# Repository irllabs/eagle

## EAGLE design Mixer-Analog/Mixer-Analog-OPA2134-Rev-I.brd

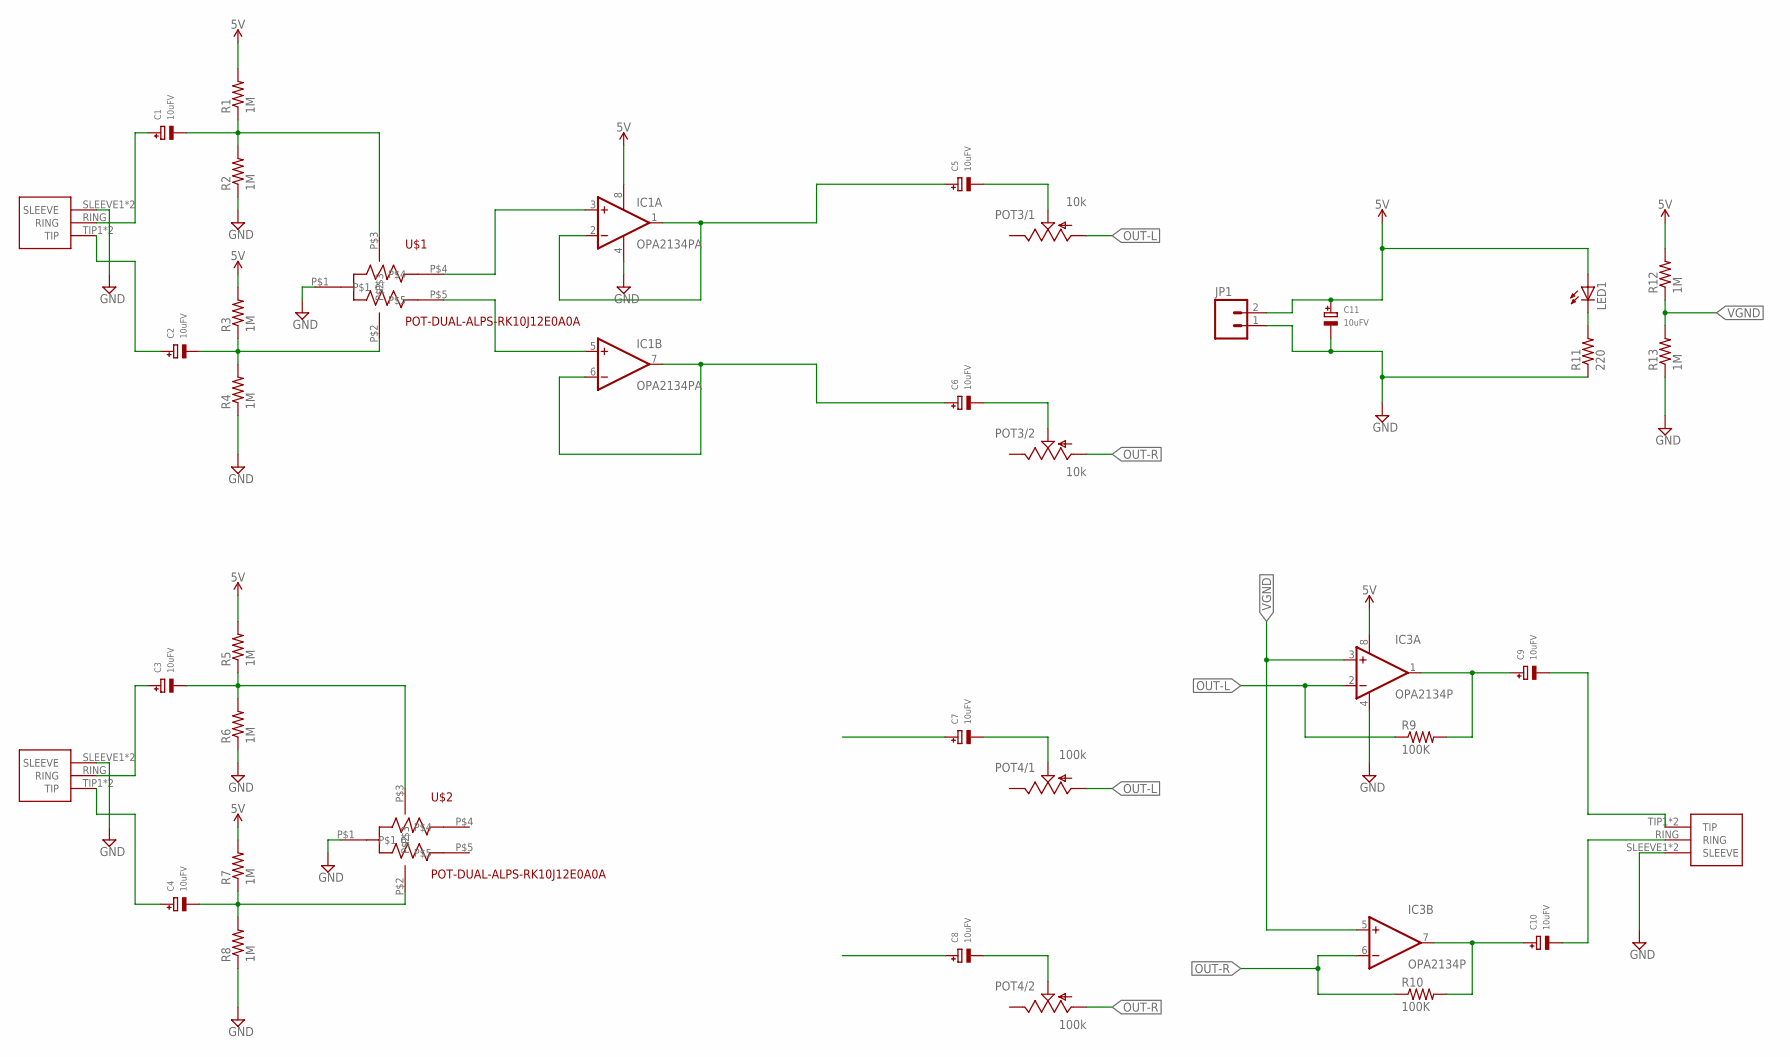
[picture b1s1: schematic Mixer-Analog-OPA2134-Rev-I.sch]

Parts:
C1, C2, C3, C4, C5, C6, C7, C8, C9, C10, C11: 10uFV; CELEC_3.5MM_8MM
IC1: OPA2134PA; DIL08
IC3: OPA2134P; DIL08
J1, J2, J3: 1/8"-F-STEREO-PCB
JP1: M02LOCK; 1X02_LOCK
LED1: LED3MM
POT3: 10k; PTV112
POT4: 100k; PTV112
R1, R3, R4, R5, R6, R7, R8, R12, R13: 1M; AXIAL-0.3EZ
R2: 1M; AXIAL-0.3
R9, R10: 100K; AXIAL-0.3EZ
R11: 220; AXIAL-0.3EZ
U$1, U$2: POT-DUAL-ALPS-RK10J12E0A0A

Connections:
5V: C11.+, IC1.8 (V+), IC3.8 (V+), JP1.2, LED1.A, R1.P$2 (2), R3.P$2 (2), R5.P$2 (2), R7.P$2 (2), R12.P$2 (2)
GND: C11.-, IC1.4 (V-), IC3.4 (V-), J1.SLEEVE1 (SLEEVE), J1.SLEEVE2 (SLEEVE), J2.SLEEVE1 (SLEEVE), J2.SLEEVE2 (SLEEVE), J3.SLEEVE1 (SLEEVE), J3.SLEEVE2 (SLEEVE), JP1.1, R2.P$1 (1), R4.P$1 (1), R6.P$1 (1), R8.P$1 (1), R11.P$1 (1), R13.P$1 (1), U$1.P$1, U$2.P$1
unnamed: C5.-, POT3.1.2 (S)
unnamed: C2.-, R3.P$1 (1), R4.P$2 (2), U$1.P$2
unnamed: C1.+, J1.RING
unnamed: C6.-, POT3.2.2 (S)
unnamed: C9.+, IC3.1 (OUT), R9.P$2 (2)
unnamed: IC1.3 (+IN), U$1.P$4
unnamed: C2.+, J1.TIP1 (TIP), J1.TIP2 (TIP)
unnamed: C7.-, POT4.1.2 (S)
unnamed: C8.-, POT4.2.2 (S)
unnamed: C4.-, R7.P$1 (1), R8.P$2 (2), U$2.P$2
unnamed: C3.+, J2.RING
unnamed: C4.+, J2.TIP1 (TIP), J2.TIP2 (TIP)
unnamed: LED1.K (C), R11.P$2 (2)
unnamed: C10.+, IC3.7 (OUT), R10.P$2 (2)
unnamed: IC1.5 (+IN), U$1.P$5
unnamed: C6.+, IC1.6 (-IN), IC1.7 (OUT)
unnamed: C3.-, R5.P$1 (1), R6.P$2 (2), U$2.P$3
unnamed: C1.-, R1.P$1 (1), R2.P$2 (2), U$1.P$3
unnamed: C9.-, J3.TIP1 (TIP), J3.TIP2 (TIP)
unnamed: C10.-, J3.RING
OUT-L: IC3.2 (-IN), POT3.1.1 (A), POT4.1.1 (A), R9.P$1 (1)
OUT-R: IC3.6 (-IN), POT3.2.1 (A), POT4.2.1 (A), R10.P$1 (1)
POT1: C5.+, IC1.1 (OUT), IC1.2 (-IN)
VGND: IC3.3 (+IN), IC3.5 (+IN), R12.P$1 (1), R13.P$2 (2)

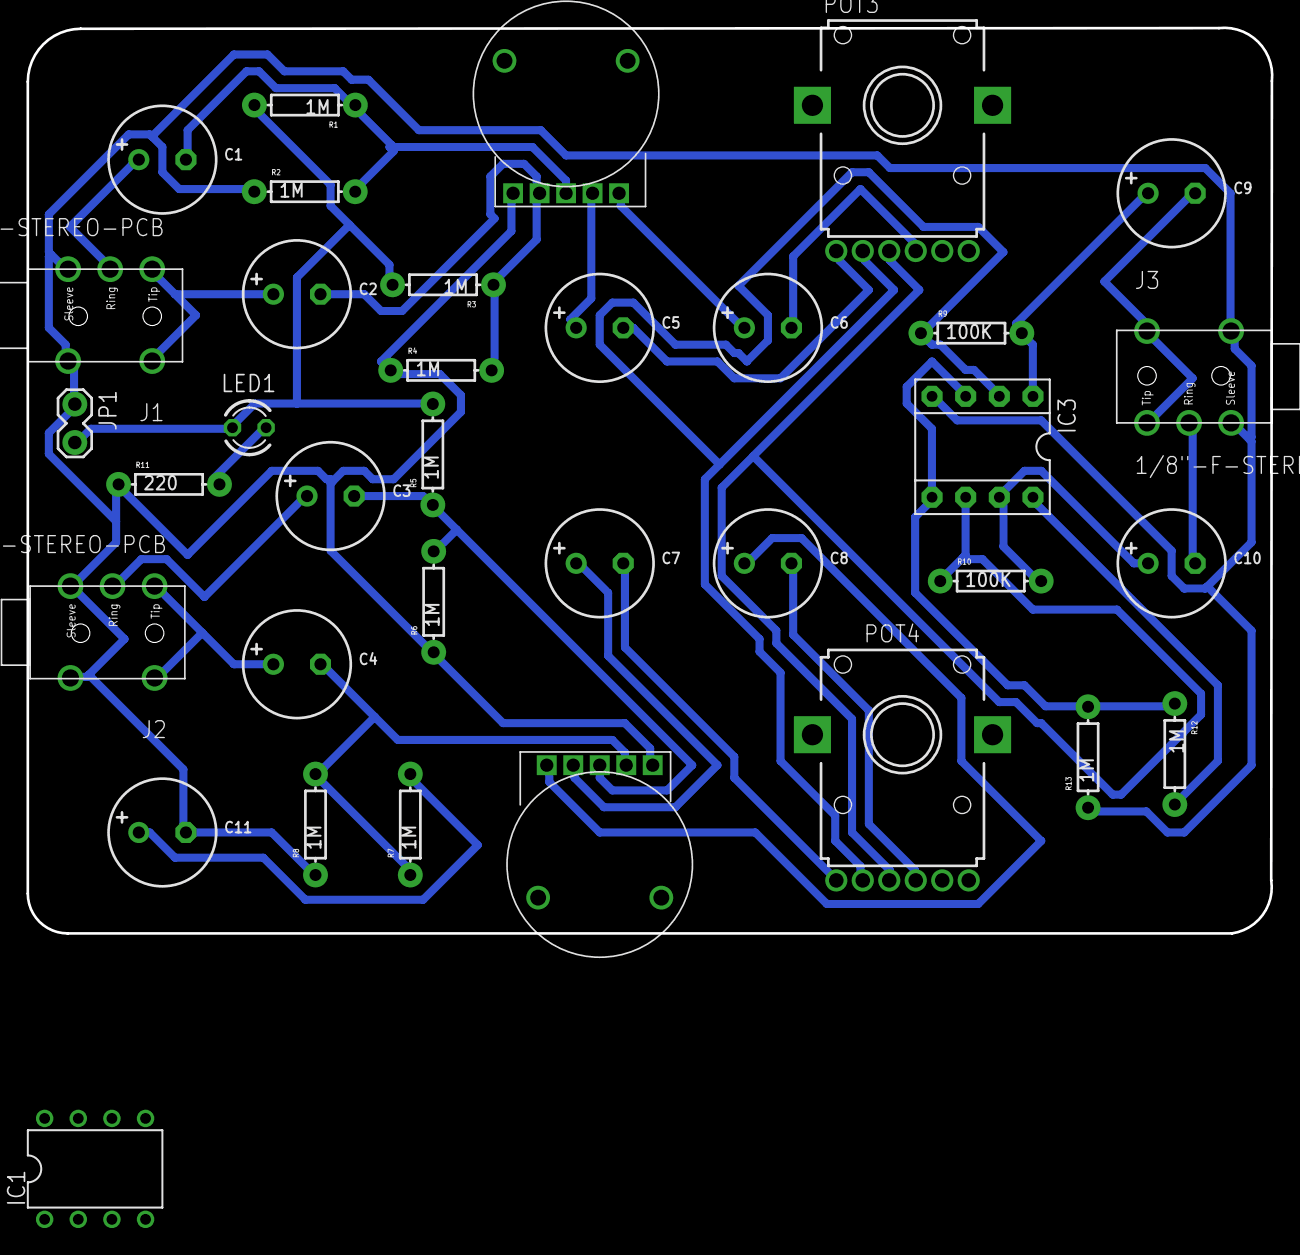
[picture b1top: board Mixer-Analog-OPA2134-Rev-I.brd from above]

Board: 2 copper layers, 94.0 x 68.4 mm, 35 parts (0 on the bottom side), 26 nets.

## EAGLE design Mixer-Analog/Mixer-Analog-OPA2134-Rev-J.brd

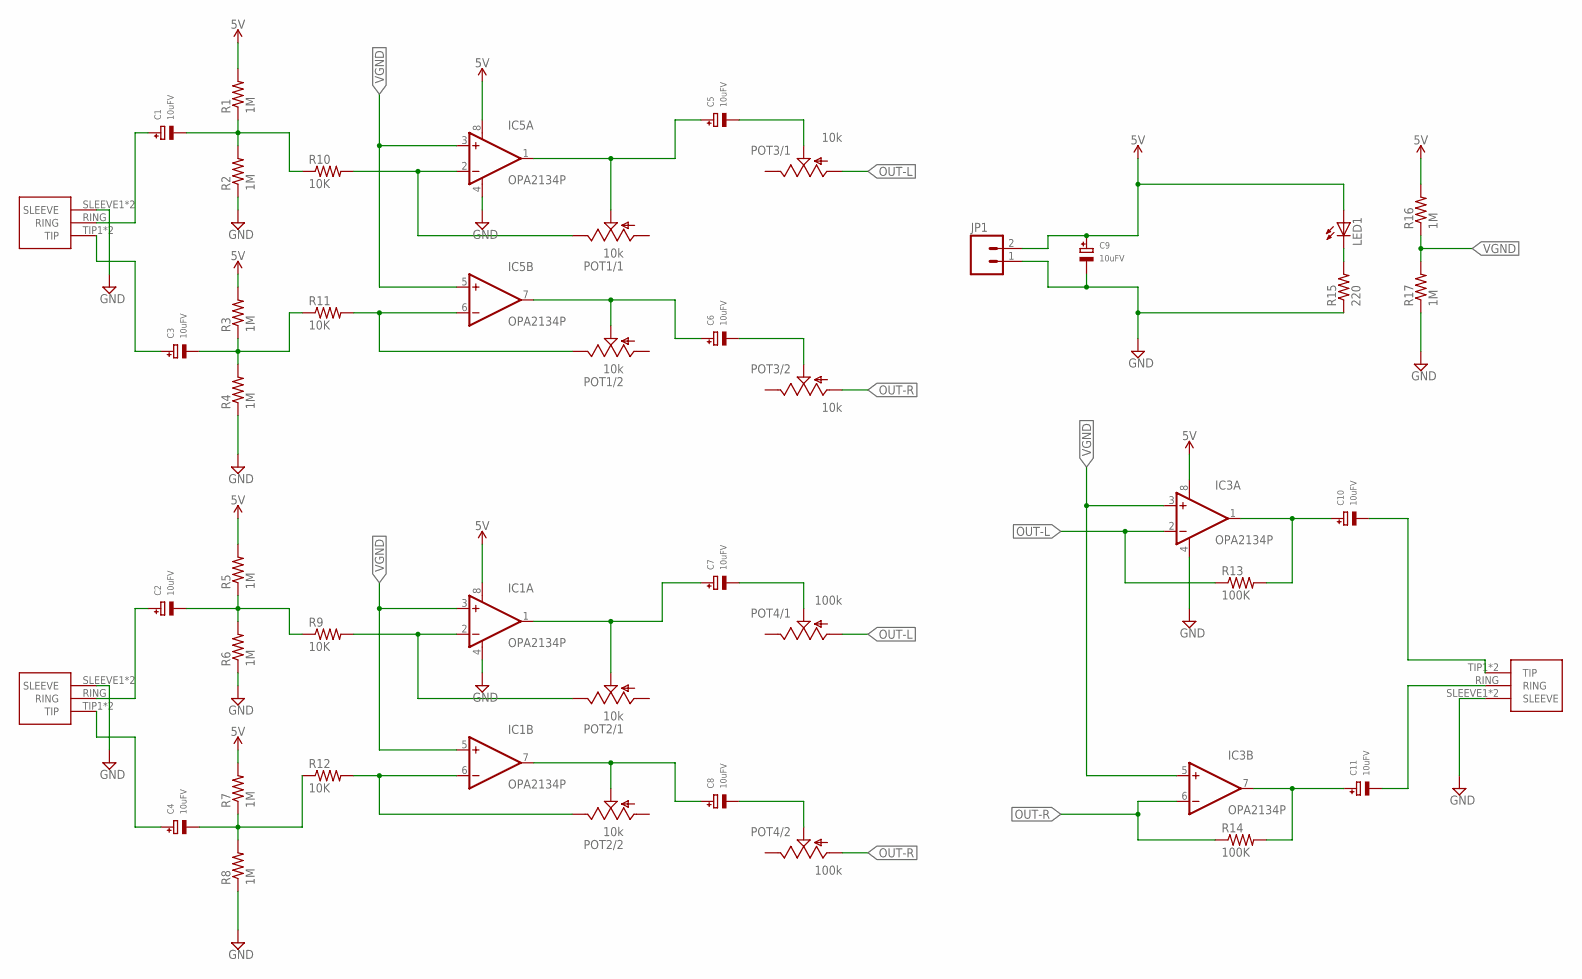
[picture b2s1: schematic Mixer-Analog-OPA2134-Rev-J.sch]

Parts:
C1, C2, C3, C4, C5, C6, C7, C8, C9, C10, C11: 10uFV; CELEC_3.5MM_8MM
IC1, IC3, IC5: OPA2134P; DIL08
J1, J2, J3: 1/8"-F-STEREO-PCB
JP1: M02LOCK; 1X02_LOCK
LED1: LED3MM
POT1, POT2, POT3: 10k; PTV112
POT4: 100k; PTV112
R1, R3, R4, R5, R6, R7, R8, R16, R17: 1M; AXIAL-0.3EZ
R2: 1M; AXIAL-0.3
R9, R10, R11, R12: 10K; AXIAL-0.3EZ
R13, R14: 100K; AXIAL-0.3EZ
R15: 220; AXIAL-0.3EZ

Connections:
5V: C9.+, IC1.8 (V+), IC3.8 (V+), IC5.8 (V+), JP1.2, LED1.A, R1.P$2 (2), R3.P$2 (2), R5.P$2 (2), R7.P$2 (2), R16.P$2 (2)
GND: C9.-, IC1.4 (V-), IC3.4 (V-), IC5.4 (V-), J1.SLEEVE1 (SLEEVE), J1.SLEEVE2 (SLEEVE), J2.SLEEVE1 (SLEEVE), J2.SLEEVE2 (SLEEVE), J3.SLEEVE1 (SLEEVE), J3.SLEEVE2 (SLEEVE), JP1.1, R2.P$1 (1), R4.P$1 (1), R6.P$1 (1), R8.P$1 (1), R15.P$1 (1), R17.P$1 (1)
unnamed: IC5.2 (-IN), POT1.1.3 (E), R10.P$2 (2)
unnamed: C5.-, POT3.1.2 (S)
unnamed: C3.-, R3.P$1 (1), R4.P$2 (2), R11.P$1 (1)
unnamed: IC5.6 (-IN), POT1.2.3 (E), R11.P$2 (2)
unnamed: C1.+, J1.RING
unnamed: C6.-, POT3.2.2 (S)
unnamed: C10.+, IC3.1 (OUT), R13.P$2 (2)
unnamed: C4.-, R7.P$1 (1), R8.P$2 (2), R12.P$1 (1)
unnamed: C3.+, J1.TIP1 (TIP), J1.TIP2 (TIP)
unnamed: C7.-, POT4.1.2 (S)
unnamed: C8.-, POT4.2.2 (S)
unnamed: C2.+, J2.RING
unnamed: C4.+, J2.TIP1 (TIP), J2.TIP2 (TIP)
unnamed: LED1.K (C), R15.P$2 (2)
unnamed: C11.+, IC3.7 (OUT), R14.P$2 (2)
unnamed: C6.+, IC5.7 (OUT), POT1.2.2 (S)
unnamed: C8.+, IC1.7 (OUT), POT2.2.2 (S)
unnamed: IC1.2 (-IN), POT2.1.3 (E), R9.P$2 (2)
unnamed: IC1.6 (-IN), POT2.2.3 (E), R12.P$2 (2)
unnamed: C2.-, R5.P$1 (1), R6.P$2 (2), R9.P$1 (1)
unnamed: C1.-, R1.P$1 (1), R2.P$2 (2), R10.P$1 (1)
unnamed: C10.-, J3.TIP1 (TIP), J3.TIP2 (TIP)
unnamed: C11.-, J3.RING
OUT-L: IC3.2 (-IN), POT3.1.1 (A), POT4.1.1 (A), R13.P$1 (1)
OUT-R: IC3.6 (-IN), POT3.2.1 (A), POT4.2.1 (A), R14.P$1 (1)
POT1: C5.+, IC5.1 (OUT), POT1.1.2 (S)
POT2: C7.+, IC1.1 (OUT), POT2.1.2 (S)
VGND: IC1.3 (+IN), IC1.5 (+IN), IC3.3 (+IN), IC3.5 (+IN), IC5.3 (+IN), IC5.5 (+IN), R16.P$1 (1), R17.P$2 (2)

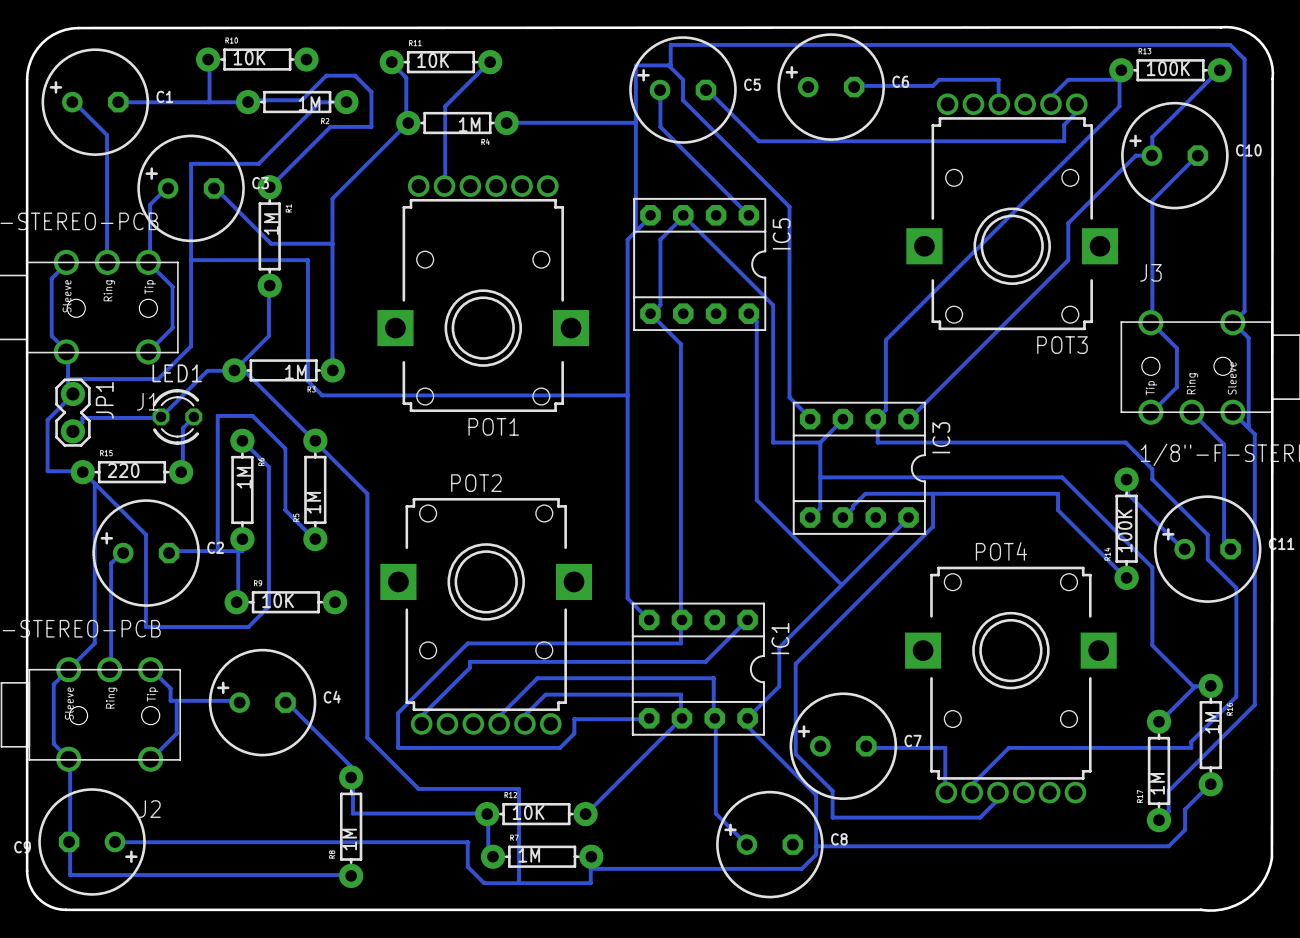
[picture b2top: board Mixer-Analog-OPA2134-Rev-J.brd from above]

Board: 2 copper layers, 96.5 x 68.4 mm, 40 parts (0 on the bottom side), 30 nets.

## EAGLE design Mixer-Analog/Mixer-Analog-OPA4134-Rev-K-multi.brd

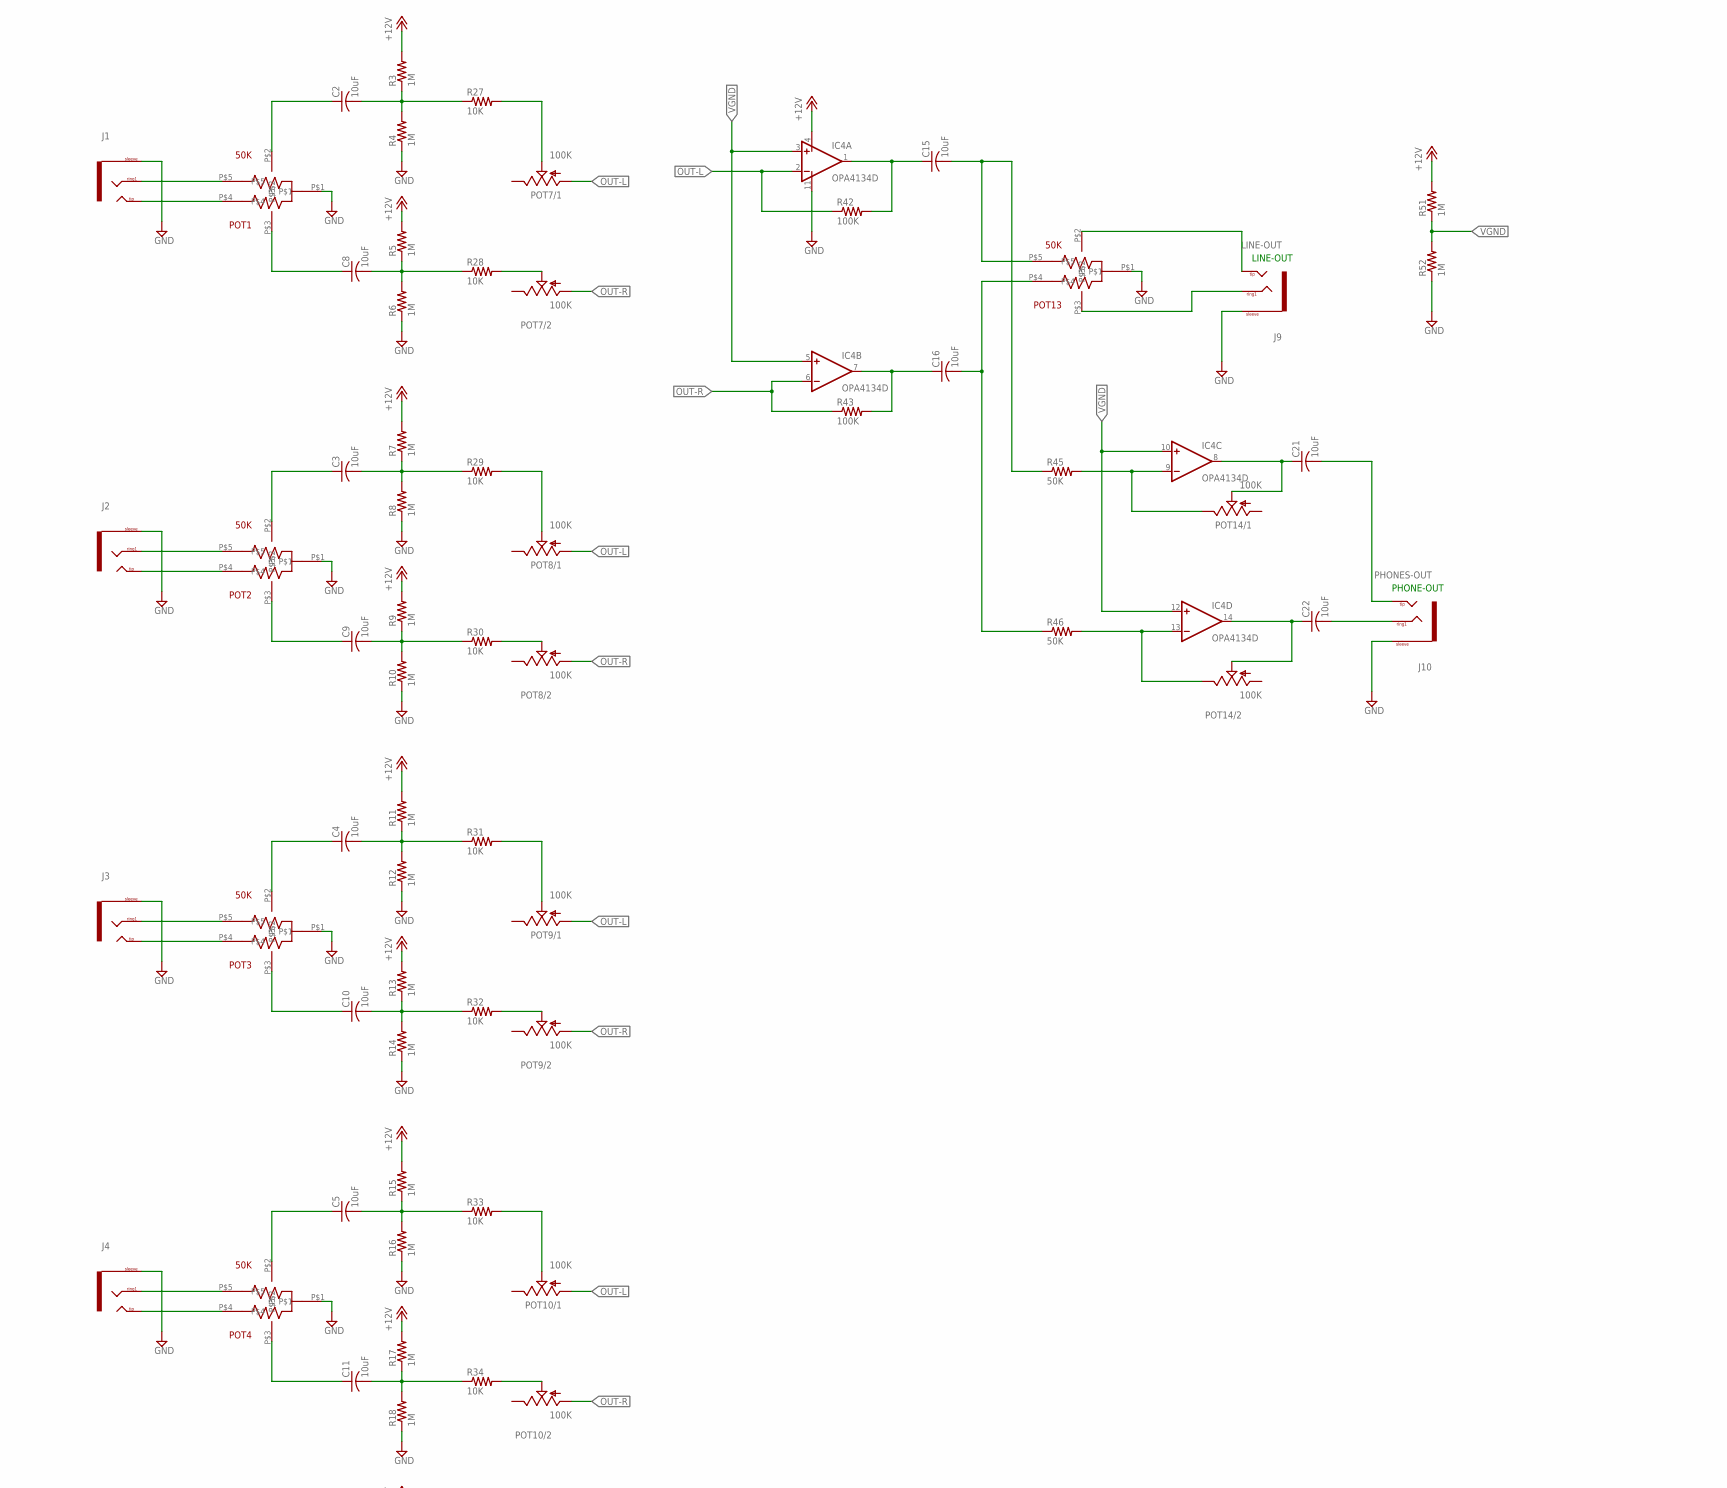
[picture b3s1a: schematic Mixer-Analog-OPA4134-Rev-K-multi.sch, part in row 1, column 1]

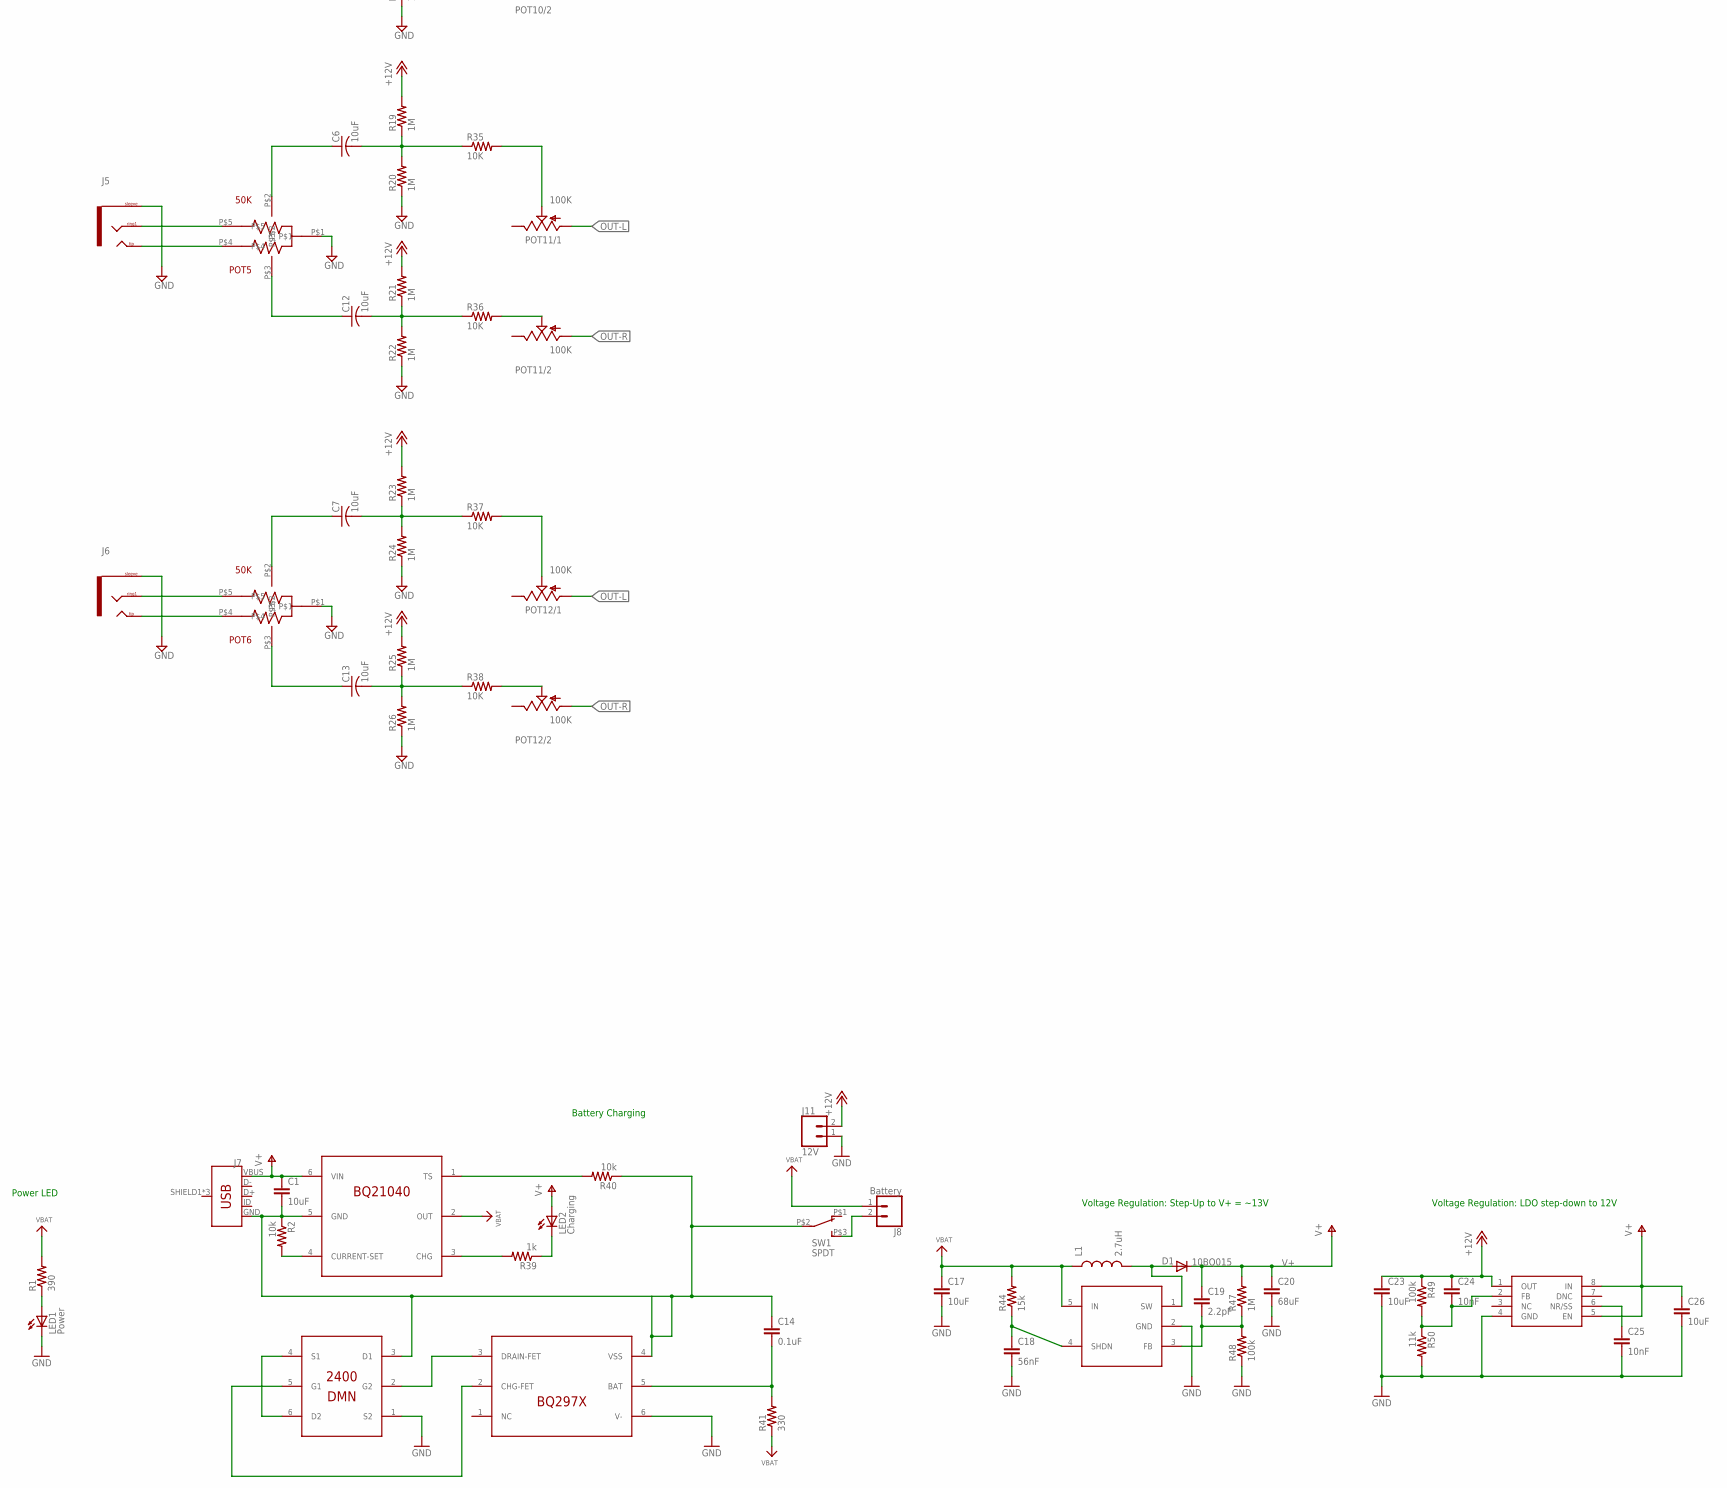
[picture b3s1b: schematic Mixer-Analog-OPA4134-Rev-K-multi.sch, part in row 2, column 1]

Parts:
C1, C17, C23, C26: 10uF; C0603
C2, C3, C4, C5, C6, C7, C8, C9, C10, C11, C12, C13, C15, C16, C21, C22: 10uF; C0805K
C14: 0.1uF; C0603
C18: 56nF; C0603
C19: 2.2pF; C0603
C20: 68uF; C1206
C24, C25: 10nF; C0603
D1: 10BQ015; SMA-DIODE
IC1: DMN2400; SOT-563
IC2: BQ21040; SOT23-6
IC3: BQ297X; WSON-6
IC4: OPA4134D; SO14
IC5: SC4503; SOT23-5
IC6: TPS7A49; MSOP-8
J1, J2, J3, J4, J5, J6: TRS-1/8"-3.5MM; TRS_SJ-3524-SMT
J7: USB_MICRO-BREDUCED_PASTE; USB-B-MICRO-SMD_RED_PASTE
J8: Battery; 1X02_LOCK
J9: LINE-OUT; TRS_SJ-3524-SMT
J10: PHONES-OUT; TRS_SJ-3524-SMT
J11: 12V; 1X02_LOCK
L1: 2.7uH; CR54-KIT
LED1: Power; LED3MM
LED2: Charging; LED3MM
POT1, POT2, POT3, POT4, POT5, POT6, POT13: 50K; POT-DUAL-ALPS-RK10J12E0A0A
POT7, POT8, POT9, POT10, POT11, POT12, POT14: 100K; PTV112
R1: 390; R0603
R2, R40: 10k; R0603
R3, R4, R5, R6, R7, R8, R9, R10, R11, R12, R13, R14, R15, R16, R17, R18, R19, R20, R21, R22, R23, R24, R25, R26, R51, R52: 1M; 0603-RES
R27, R28, R29, R30, R31, R32, R33, R34, R35, R36, R37, R38: 10K; 0603-RES
R39: 1k; R0603
R41: 330; R0603
R42, R43: 100K; 0603-RES
R44: 15k; R0603
R45, R46: 50K; 0603-RES
R47: 1M; R0603
R48, R49: 100k; R0603
R50: 11k; R0603
SW1: SPDT; SWITCH_SPDT_CL-SB-12B

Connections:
+12V: C23.1, C24.1, IC4.4 (V+), IC6.1 (OUT), J11.2, R3.2, R5.2, R7.2, R9.2, R11.2, R13.2, R15.2, R17.2, R19.2, R21.2, R23.2, R25.2, R49.1, R51.2
GND: C17.2, C18.2, C20.2, C23.2, C25.2, C26.2, IC1.1 (S2), IC3.6 (V-), IC4.11 (V-), IC6.4 (GND), J1.1 (SLEEVE), J2.1 (SLEEVE), J3.1 (SLEEVE), J4.1 (SLEEVE), J5.1 (SLEEVE), J6.1 (SLEEVE), J9.1 (SLEEVE), J10.1 (SLEEVE), J11.1, LED1.K (C), POT1.P$1, POT2.P$1, POT3.P$1, POT4.P$1, POT5.P$1, POT6.P$1, POT13.P$1, R4.1, R6.1, R8.1, R10.1, R12.1, R14.1, R16.1, R18.1, R20.1, R22.1, R24.1, R26.1, R48.1, R50.2, R52.1
GND1: C1.2, C14.1, IC1.3 (D1), IC2.5 (GND), IC3.4 (VSS), J7.GND, R2.1, R40.1, SW1.P$2 (2)
unnamed: C8.1, POT1.P$3
unnamed: J8.2, SW1.P$3 (3)
unnamed: C8.2, R5.1, R6.2, R28.1
unnamed: J1.3 (RING1), POT1.P$5
unnamed: C15.1, IC4.1 (OUT), R42.2
unnamed: C2.1, POT1.P$2
unnamed: J1.2 (TIP), J1.4 (TIP), POT1.P$4
unnamed: C2.2, R3.1, R4.2, R27.1
unnamed: IC4.13 (-IN), POT14.2.3 (E), R46.2
unnamed: J9.2 (TIP), J9.4 (TIP), POT13.P$2
unnamed: C16.1, IC4.7 (OUT), R43.2
unnamed: J9.3 (RING1), POT13.P$3
unnamed: POT7.2.2 (S), R28.2
unnamed: C22.2, J10.3 (RING1)
unnamed: C9.2, R9.1, R10.2, R30.1
unnamed: C21.2, J10.2 (TIP), J10.4 (TIP)
unnamed: C21.1, IC4.8 (OUT), POT14.1.2 (S)
unnamed: C22.1, IC4.14 (OUT), POT14.2.2 (S)
unnamed: J2.3 (RING1), POT2.P$5
unnamed: POT8.1.2 (S), R29.2
unnamed: C9.1, POT2.P$3
unnamed: C3.1, POT2.P$2
unnamed: J2.2 (TIP), J2.4 (TIP), POT2.P$4
unnamed: C3.2, R7.1, R8.2, R29.1
unnamed: POT8.2.2 (S), R30.2
unnamed: C10.2, R13.1, R14.2, R32.1
unnamed: J3.3 (RING1), POT3.P$5
unnamed: POT9.1.2 (S), R31.2
unnamed: C10.1, POT3.P$3
unnamed: C4.1, POT3.P$2
unnamed: J3.2 (TIP), J3.4 (TIP), POT3.P$4
unnamed: C4.2, R11.1, R12.2, R31.1
unnamed: POT9.2.2 (S), R32.2
unnamed: POT7.1.2 (S), R27.2
unnamed: C11.2, R17.1, R18.2, R34.1
unnamed: J4.3 (RING1), POT4.P$5
unnamed: POT10.1.2 (S), R33.2
unnamed: C15.2, POT13.P$5, R45.1
unnamed: C11.1, POT4.P$3
unnamed: C5.1, POT4.P$2
unnamed: J4.2 (TIP), J4.4 (TIP), POT4.P$4
unnamed: C5.2, R15.1, R16.2, R33.1
unnamed: POT10.2.2 (S), R34.2
unnamed: C12.2, R21.1, R22.2, R36.1
unnamed: J5.3 (RING1), POT5.P$5
unnamed: POT11.1.2 (S), R35.2
unnamed: C12.1, POT5.P$3
unnamed: C6.1, POT5.P$2
unnamed: J5.2 (TIP), J5.4 (TIP), POT5.P$4
unnamed: C6.2, R19.1, R20.2, R35.1
unnamed: POT11.2.2 (S), R36.2
unnamed: C13.2, R25.1, R26.2, R38.1
unnamed: J6.3 (RING1), POT6.P$5
unnamed: POT12.1.2 (S), R37.2
unnamed: C13.1, POT6.P$3
unnamed: C7.1, POT6.P$2
unnamed: J6.2 (TIP), J6.4 (TIP), POT6.P$4
unnamed: C7.2, R23.1, R24.2, R37.1
unnamed: POT12.2.2 (S), R38.2
unnamed: LED1.A, R1.1
unnamed: D1.A, IC5.1 (SW), L1.P$2 (2)
unnamed: C18.1, IC5.4 (SHDN), R44.1
unnamed: C19.2, IC5.3 (FB), R47.1, R48.2
unnamed: C24.2, IC6.2 (FB), R49.2, R50.1
unnamed: C25.1, IC6.6 (NR/SS)
unnamed: LED2.K (C), R39.1
unnamed: IC2.3 (CHG), R39.2
unnamed: IC2.1 (TS), R40.2
unnamed: IC2.4 (CURRENT-SET), R2.2
unnamed: C14.2, IC3.5 (BAT), R41.2
unnamed: IC1.4 (S1), IC1.6 (D2)
unnamed: IC1.5 (G1), IC3.2 (CHG-FET)
unnamed: IC1.2 (G2), IC3.3 (DRAIN-FET)
OUT-L: IC4.2 (-IN), POT7.1.1 (A), POT8.1.1 (A), POT9.1.1 (A), POT10.1.1 (A), POT11.1.1 (A), POT12.1.1 (A), R42.1
OUT-L1: IC4.9 (-IN), POT14.1.3 (E), R45.2
OUT-R: IC4.6 (-IN), POT7.2.1 (A), POT8.2.1 (A), POT9.2.1 (A), POT10.2.1 (A), POT11.2.1 (A), POT12.2.1 (A), R43.1
OUT-R1: C16.2, POT13.P$4, R46.1
V+: C1.1, C19.1, C20.1, C26.1, D1.C, IC2.6 (VIN), IC6.5 (EN), IC6.8 (IN), J7.VBUS, LED2.A, R47.2
VBAT: C17.1, IC2.2 (OUT), IC5.5 (IN), J8.1, L1.P$1 (1), R1.2, R41.1, R44.2
VGND: IC4.3 (+IN), IC4.5 (+IN), IC4.10 (+IN), IC4.12 (+IN), R51.1, R52.2

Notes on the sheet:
LINE-OUT
PHONE-OUT
Voltage Regulation: Step-Up to V+ = ~13V
Power LED
Voltage Regulation: LDO step-down to 12V
Battery Charging

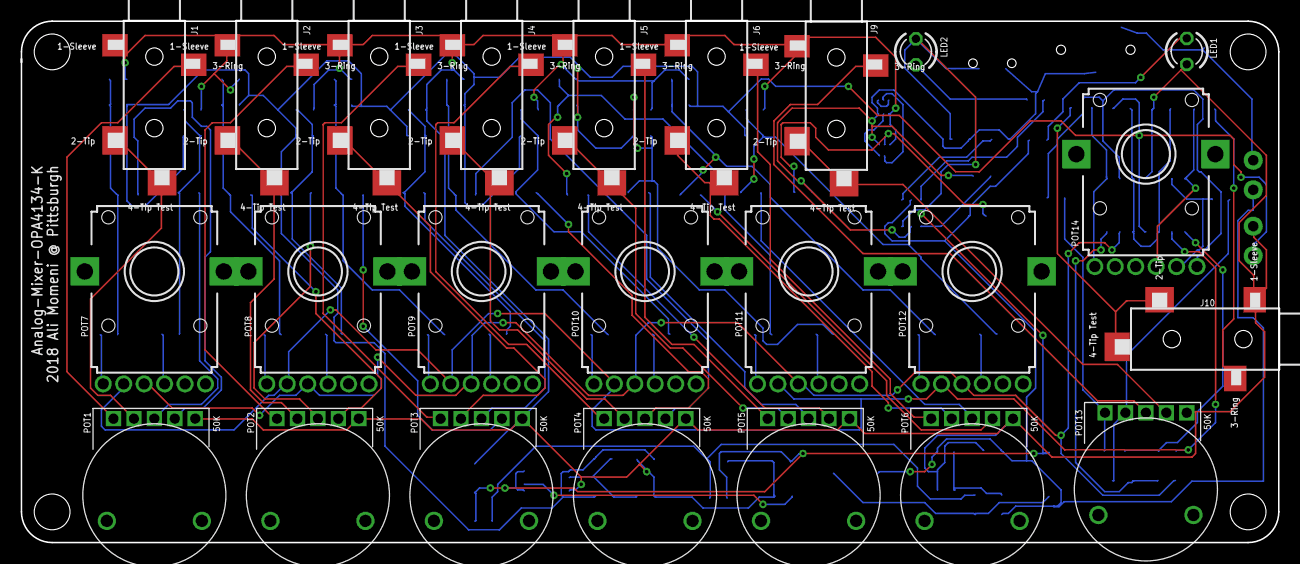
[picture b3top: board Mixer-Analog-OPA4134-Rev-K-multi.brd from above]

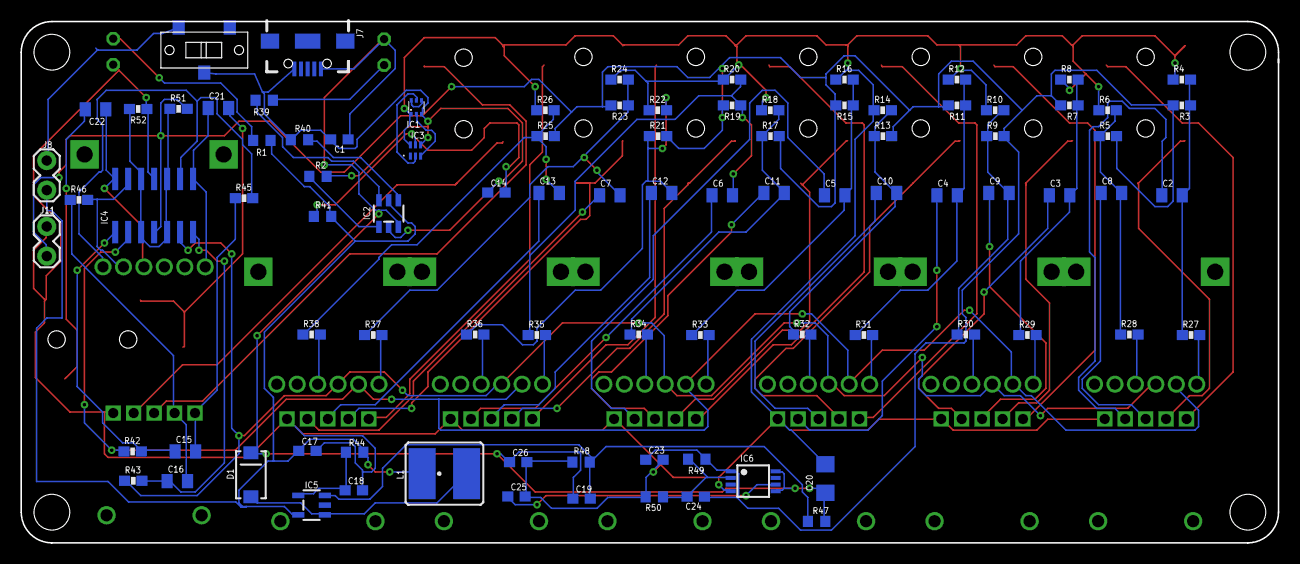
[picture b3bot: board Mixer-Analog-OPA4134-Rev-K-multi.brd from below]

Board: 2 copper layers, 123.0 x 51.0 mm, 114 parts (90 on the bottom side), 83 nets.

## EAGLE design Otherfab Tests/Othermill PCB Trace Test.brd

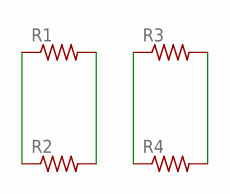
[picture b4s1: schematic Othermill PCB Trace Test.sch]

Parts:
R1, R2, R3, R4: R-US_0204/2V; 0204V

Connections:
unnamed: R1.1, R2.1
unnamed: R1.2, R2.2
unnamed: R3.1, R4.1
unnamed: R3.2, R4.2

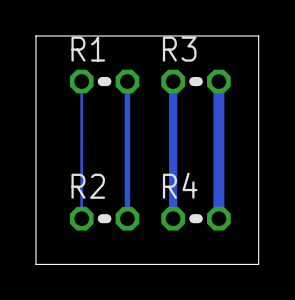
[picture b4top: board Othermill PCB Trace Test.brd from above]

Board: 2 copper layers, 12.4 x 12.7 mm, 4 parts (0 on the bottom side), 4 nets.

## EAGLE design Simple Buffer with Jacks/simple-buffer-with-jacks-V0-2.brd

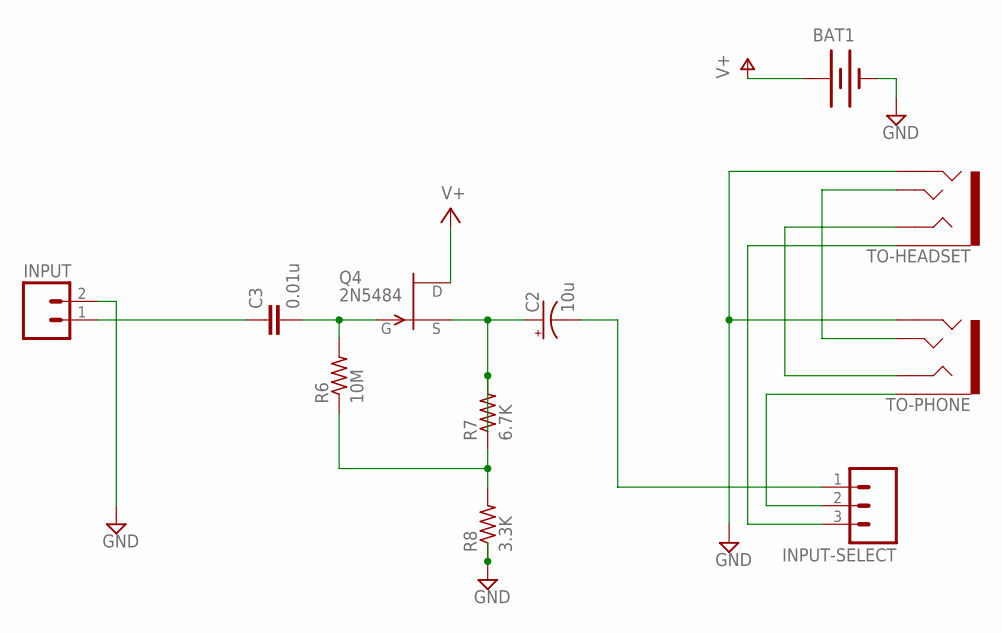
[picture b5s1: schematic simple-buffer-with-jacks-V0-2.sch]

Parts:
BAT1: BATTERYAAA-KIT; BATTERY-AAA-KIT
C2: 10u; CPOL-RADIAL-10UF-25V
C3: 0.01u; C5B3
INPUT: M02LOCK; 1X02_LOCK
INPUT-SELECT: M03LOCK; 1X03_LOCK
Q4: 2N5484; TO92-
R6: 10M; 0414V
R7: 6.7K; 0414V
R8: 3.3K; 0414V
TO-HEADSET: AUDIO-JACK3; AUDIO-JACK-TRRS-SMD
TO-PHONE: AUDIO-JACK3; AUDIO-JACK-TRRS-SMD

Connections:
GND: BAT1.GND@1 (-), INPUT.2, R8.1, TO-HEADSET.RING2, TO-PHONE.RING2
JFET-GATE: C3.2, Q4.1 (G), R6.2
JFET-SOURCE: C2.1 (+), Q4.2 (S), R7.2
unnamed: C3.1, INPUT.1
unnamed: C2.2 (-), INPUT-SELECT.1
unnamed: INPUT-SELECT.3, TO-HEADSET.EARTH
unnamed: TO-HEADSET.TIP, TO-PHONE.TIP
unnamed: TO-HEADSET.RING1, TO-PHONE.RING1
unnamed: R6.1, R7.1, R8.2
TO-PHONE: INPUT-SELECT.2, TO-PHONE.EARTH
V+: BAT1.PWR@1 (+), Q4.3 (D)

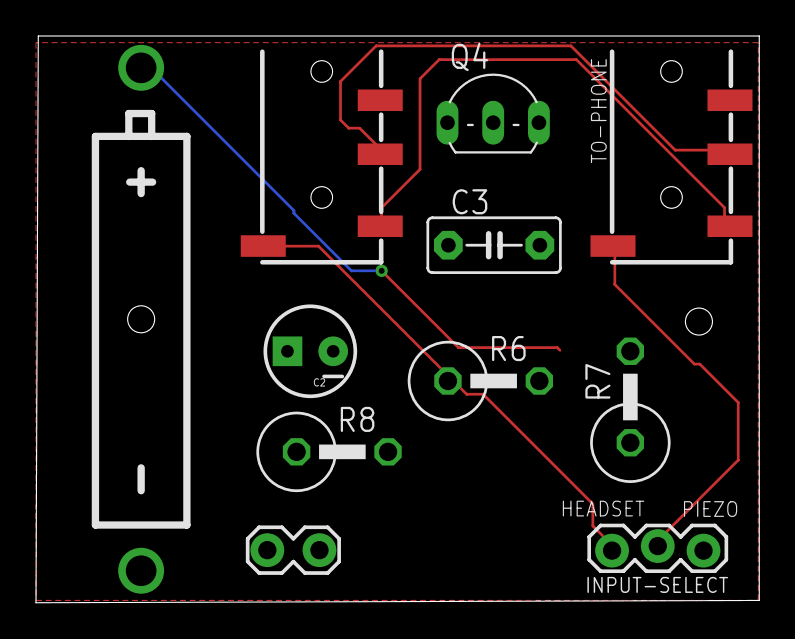
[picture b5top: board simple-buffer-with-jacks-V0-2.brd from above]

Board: 2 copper layers, 40.2 x 31.5 mm, 11 parts (0 on the bottom side), 11 nets.

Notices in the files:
parts and their libraries:
SparkFun-Passives: Licensing: Creative Commons ShareAlike 4.0 International - https://creativecommons.org/licenses/by-sa/4.0
microbuilder: This work is placed in the public domain, and may be freely used for commercial and non-commercial work with the following conditions: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
